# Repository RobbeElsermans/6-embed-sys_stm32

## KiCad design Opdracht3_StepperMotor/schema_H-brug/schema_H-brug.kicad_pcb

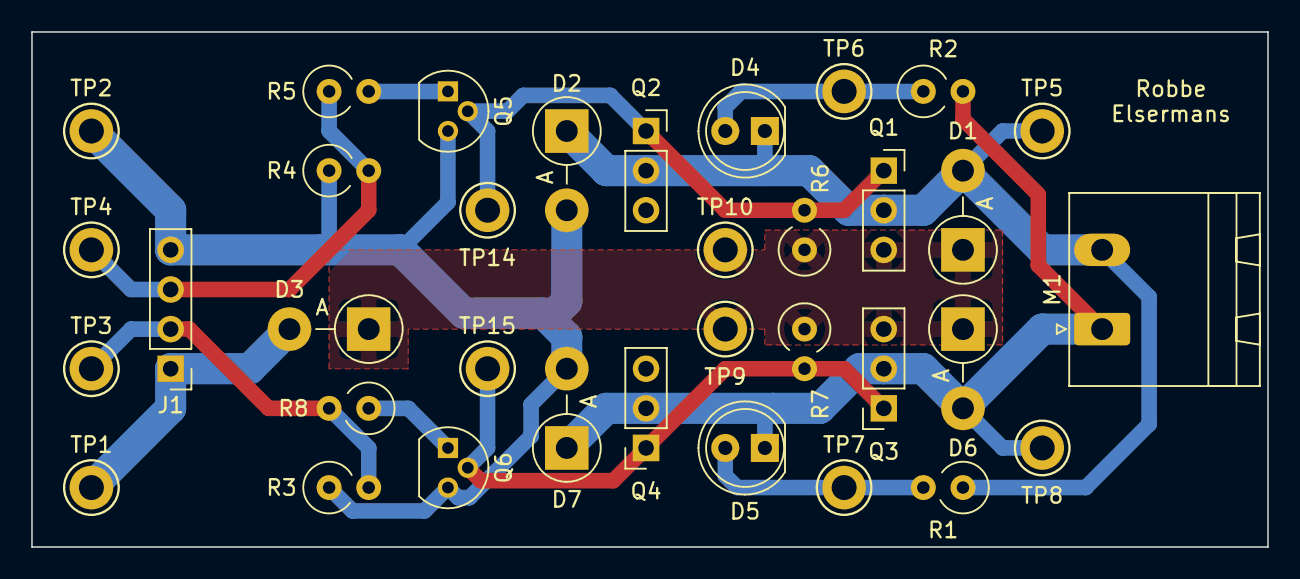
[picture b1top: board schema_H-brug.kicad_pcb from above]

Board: 2 copper layers, 79.2 x 33.0 mm, 35 parts (0 on the bottom side), 13 nets.

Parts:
D1, D2, D3, D6, D7: D; D_5W_P5.08mm_Vertical_AnodeUp
D4, D5: LED; LED_D5.0mm
J1: Conn_01x04; PinHeader_1x04_P2.54mm_Vertical
M1: Motor_DC; PhoenixContact_MSTBA_2,5_2-G-5,08_1x02_P5.08mm_Horizontal
Q1, Q3: Q_PMOS_GDS; PinSocket_1x03_P2.54mm_Vertical
Q2, Q4: Q_NMOS_GDS; PinSocket_1x03_P2.54mm_Vertical
Q5, Q6: Q_NPN_BCE; TO-92
R1, R2: 560; R_Axial_DIN0309_L9.0mm_D3.2mm_P2.54mm_Vertical
R3, R4, R6, R7: 10k; R_Axial_DIN0309_L9.0mm_D3.2mm_P2.54mm_Vertical
R5, R8: 330; R_Axial_DIN0309_L9.0mm_D3.2mm_P2.54mm_Vertical
TP1, TP2, TP3, TP4, TP5, TP6, TP7, TP8, TP9, TP10, TP14, TP15: TestPoint; TestPoint_Keystone_5005-5009_Compact

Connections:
EN_L: J1.2, R3.2, R8.2, TP3.1
EN_R: J1.3, R4.2, R5.1, TP4.1
GND: D2.2 (A), D7.2 (A), J1.4, Q2.3 (S), Q4.3 (S), Q5.3 (E), Q6.3 (E), R3.1, R4.1, TP2.1
unnamed: D1.1 (K), D3.1 (K), D6.1 (K), Q1.3 (S), Q3.3 (S), R6.1, R7.1, TP9.1, TP10.1
unnamed: D1.2 (A), D2.1 (K), D4.1 (K), M1.2 (-), Q1.2 (D), Q2.2 (D), R1.1, TP5.1
unnamed: D4.2 (A), R2.1, TP6.1
unnamed: D5.1 (K), D6.2 (A), D7.1 (K), M1.1 (+), Q3.2 (D), Q4.2 (D), R2.2, TP8.1
unnamed: D5.2 (A), R1.2, TP7.1
unnamed: Q1.1 (G), Q2.1 (G), Q5.2 (C), R6.2, TP14.1
unnamed: Q3.1 (G), Q4.1 (G), Q6.2 (C), R7.2, TP15.1
unnamed: Q5.1 (B), R5.2
unnamed: Q6.1 (B), R8.1
VCC_MOTOR: D3.2 (A), J1.1, TP1.1

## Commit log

2023-04-24 Add H_Bridge project
2023-04-29 update schema
2023-05-08 Einde
